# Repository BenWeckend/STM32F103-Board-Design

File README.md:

# STM32F103 Board Design

## Überblick

Hardware-Referenzdesign und Firmware für ein Übungs-Entwicklungsboard auf Basis des **STM32F103C8T6** mit CAN, USB, I²C (BME280) und weiterer Peripherie.

Das Repository enthält:

* KiCad-Schaltplan und PCB-Design
* Gerber- und Fertigungsdaten
* Stückliste (BOM)
* STM32CubeIDE Firmware-Projekt
* Tauri Desktop-Anwendung zur Kommunikation mit dem Board

---

## Hardware

### Schaltplan

<p align="center">
  
</p>

<p align="center">
  Vollständiger Schaltplan des STM32F103-Boards mit CAN, USB, Spannungsversorgung und BME280-Sensor.
</p>

### 3D-Ansicht der Platine

<p align="center">
  
</p>

<p align="center">
  3D-Vorschau der fertig bestückten Leiterplatte aus KiCad.
</p>

---

## Projektstruktur

| Ordner                 | Beschreibung                               |
| ---------------------- | ------------------------------------------ |
| `kicad/`               | Schaltplan, PCB-Layout und Fertigungsdaten |
| `firmware/`            | STM32CubeIDE-Projekt                       |
| `tauri-app/`           | Desktop-Anwendung (Rust + Frontend)        |

---

## Hauptfunktionen

### Mikrocontroller

* `STM32F103C8T6` (LQFP48)

### Kommunikation

* CAN-Bus über `TJA1051`
* USB Micro-B Device Interface

### Sensorik

* `BME280` (I²C)

  * Temperatur
  * Luftdruck
  * Luftfeuchtigkeit

### Spannungsversorgung

* `AMS1117-3.3`
* Onboard 3.3V-Regler

### Debugging & Programmierung

* SWD Header
* ST-Link kompatibel
* STM32CubeProgrammer kompatibel

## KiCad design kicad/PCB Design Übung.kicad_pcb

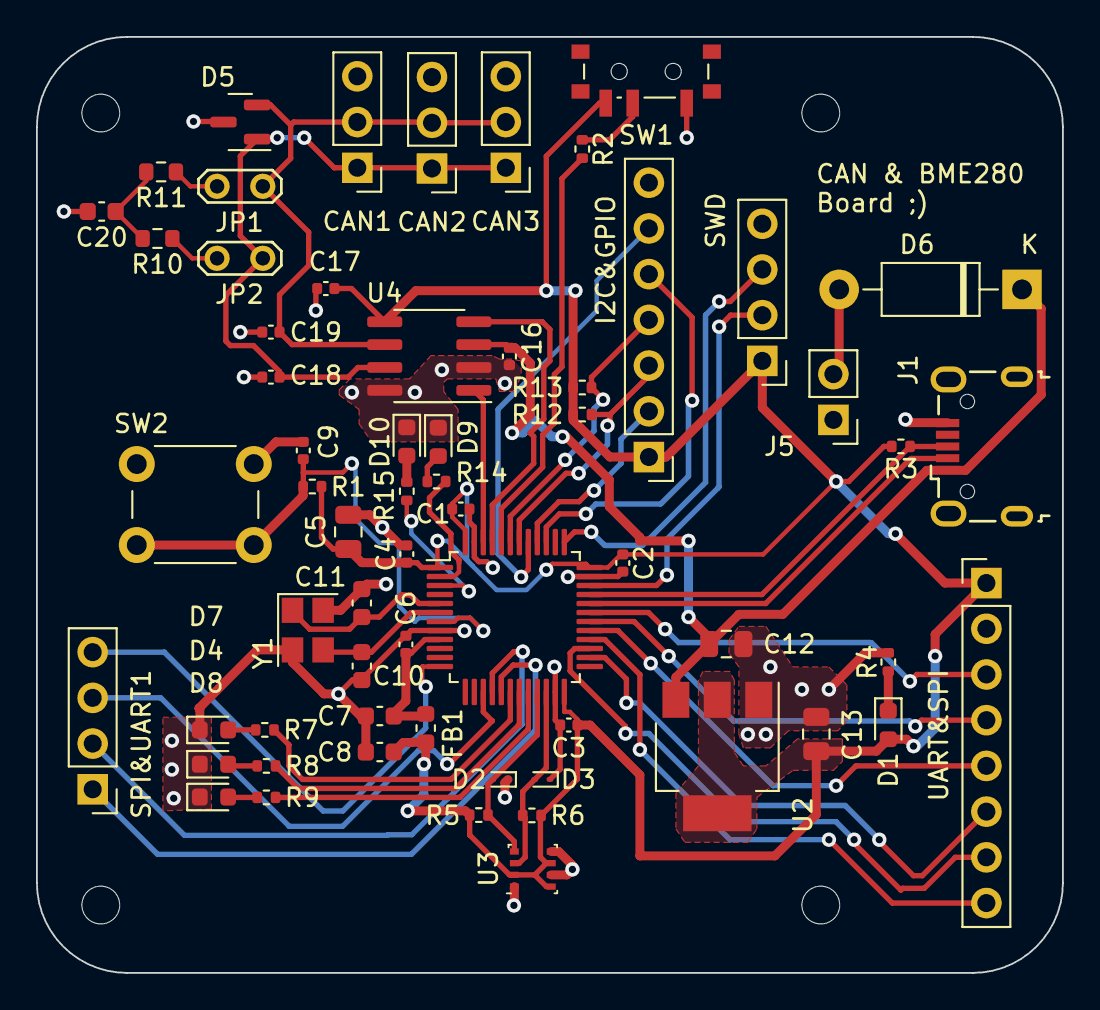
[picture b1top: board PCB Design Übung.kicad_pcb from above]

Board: 2 copper layers, 57.0 x 52.0 mm, 66 parts (0 on the bottom side), 49 nets.

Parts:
C1, C2, C3, C4, C9, C16, C17: 100n; C_0402_1005Metric
C5: 10u; C_0805_2012Metric
C6: 10n; C_0402_1005Metric
C7, C8: 1u; C_0603_1608Metric
C10, C11: 10p; C_0603_1608Metric
C12, C13: 22u; C_0805_2012Metric
C18, C19: 100p; C_0402_1005Metric
C20: 4n7; C_0603_1608Metric
CAN1, CAN2, CAN3: Conn_01x03; PinHeader_1x03_P2.54mm_Vertical
D1: LED-Green; LED_0603_1608Metric
D2, D3: ESD9B3.3ST5G; D_SOD-923
D4, D7, D8: LED_B; LED_0603_1608Metric
D5: NUP2105LT1G; SOT-23
D6: 1N5818; D_DO-41_SOD81_P10.16mm_Horizontal
D9: LED_G; LED_0603_1608Metric
D10: LED_R; LED_0603_1608Metric
FB1: 120R; L_0603_1608Metric
H1, H2, H3, H4: MountingHole; MountingHole_2.1mm
I2C&GPIO: Conn_01x07; PinHeader_1x07_P2.54mm_Vertical
J1: USB_B_Micro; USB_Micro-B_Wuerth_629105150521
J5: Conn_01x02_Pin; PinHeader_1x02_P2.54mm_Vertical
JP1, JP2: Jumper_2_Bridged; TestPoint_2Pads_Pitch2.54mm_Drill0.8mm
R1, R2: 10k; R_0402_1005Metric
R3: 1k5; R_0402_1005Metric
R4, R14: 0.1k; R_0402_1005Metric
R5, R6, R12, R13: 4k7; R_0402_1005Metric
R7, R8, R9: 10ohm; R_0402_1005Metric
R10, R11: 60ohm; R_0603_1608Metric
R15: 220ohm; R_0402_1005Metric
SPI&UART1: Conn_01x04_Pin; PinHeader_1x04_P2.54mm_Vertical
SW1: SW_SPDT; SW_SPDT_PCM12
SW2: SW_Push; SW_PUSH_6mm
SWD: Conn_01x04_Pin; PinHeader_1x04_P2.54mm_Vertical
U1: STM32F103C8T6; LQFP-48_7x7mm_P0.5mm
U2: AMS1117-3.3; SOT-223-3_TabPin2
U3: BME280; Bosch_LGA-8_2.5x2.5mm_P0.65mm_ClockwisePinNumbering
U4: TJA1051T-3; SOIC-8_3.9x4.9mm_P1.27mm
UART&SPI: Conn_01x08; PinHeader_1x08_P2.54mm_Vertical
Y1: 16MHz; Crystal_SMD_3225-4Pin_3.2x2.5mm

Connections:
+3.3V: C1.1, C2.1, C3.1, C4.1, C5.1, C8.1, C13.1, C17.1, D1.2 (A), FB1.2, I2C&GPIO.1, R1.2, R3.1, R5.1, R6.1, R12.1, R13.1, SW1.3 (C), SWD.1, U1.1 (VBAT), U1.24 (VDD), U1.36 (VDD), U1.48 (VDD), U2.2 (VO), U3.2 (CSB), U3.6 (VDDIO), U3.8 (VDD), U4.5 (VIO), UART&SPI.1
+3.3VA: C6.1, C7.1, FB1.1, U1.9 (VDDA)
/BOOT0: R2.2, U1.44 (BOOT0)
/CANH: C18.1, CAN1.1, CAN2.1, CAN3.1, D5.1 (K), JP2.1 (A), U4.7 (CANH)
/CANL: C19.1, CAN1.2, CAN2.2, CAN3.2, D5.2 (K), JP1.1 (A), U4.6 (CANL)
/HSE_IN: C11.1, U1.5 (PD0), Y1.1
/HSE_OUT: C10.1, U1.6 (PD1), Y1.3
/PWR_LED_K: D1.1 (K), R4.1
/SWCLK: SWD.3, U1.37 (PA14)
/SWDIO: SWD.2, U1.34 (PA13)
/SW_BOOT0: R2.1, SW1.2 (B)
/USB_D+: J1.3 (D+), R3.2, U1.33 (PA12)
/USB_D-: J1.2 (D-), U1.32 (PA11)
CAN_RX: U1.45 (PB8), U4.4 (RXD)
CAN_TX: U1.46 (PB9), U4.1 (TXD)
GND: C1.2, C2.2, C3.2, C4.2, C5.2, C6.2, C7.2, C8.2, C9.2, C10.2, C11.2, C12.2, C13.2, C16.2, C17.2, C18.2, C19.2, C20.2, CAN1.3, CAN2.3, CAN3.3, D2.1 (A1), D3.1 (A1), D4.1 (K), D5.3 (A), D7.1 (K), D8.1 (K), D9.1 (K), D10.1 (K), I2C&GPIO.7, J1.5 (GND), J5.1, R4.2, SW1.1 (A), SW2.1, SWD.4, U1.8 (VSSA), U1.23 (VSS), U1.35 (VSS), U1.47 (VSS), U2.1 (GND), U3.1 (GND), U3.5 (SDO), U3.7 (GND), U4.2 (GND), U4.8 (S), UART&SPI.2, Y1.2, Y1.4
I2C1_SCL: I2C&GPIO.3, R12.2, U1.42 (PB6)
I2C1_SDA: I2C&GPIO.4, R13.2, U1.43 (PB7)
NRST: C9.1, R1.1, SW2.2, U1.7 (NRST)
unnamed: C20.1, R10.2, R11.2
unnamed: D4.2 (A), R8.2
unnamed: D6.2 (A), J5.2
unnamed: D7.2 (A), R7.2
unnamed: D8.2 (A), R9.2
unnamed: D9.2 (A), R14.2
unnamed: D10.2 (A), R15.2
unnamed: JP1.2 (B), R11.1
unnamed: JP2.2 (B), R10.1
unnamed: R7.1, U1.18 (PB0)
unnamed: R8.1, U1.19 (PB1)
unnamed: R9.1, U1.20 (PB2)
unnamed: R14.1, U1.2 (PC13)
unnamed: R15.1, U1.3 (PC14)
PB3: I2C&GPIO.5, U1.39 (PB3)
PB4: I2C&GPIO.2, U1.40 (PB4)
PB5: I2C&GPIO.6, U1.41 (PB5)
SCL_I2C: D2.2 (A2), R5.2, U1.21 (PB10), U3.4 (SCK)
SDA_I2C: D3.2 (A2), R6.2, U1.22 (PB11), U3.3 (SDI)
SPI1_MISO: SPI&UART1.2, U1.16 (PA6)
SPI1_MOSI: SPI&UART1.1, U1.17 (PA7)
SPI1_SCK: SPI&UART1.3, U1.15 (PA5)
SPI2_MISO: U1.27 (PB14), UART&SPI.7
SPI2_MOSI: U1.28 (PB15), UART&SPI.8
SPI2_SCK: U1.26 (PB13), UART&SPI.6
UART_TX: SPI&UART1.4, U1.12 (PA2)
USART1_CK: U1.29 (PA8), UART&SPI.5
USART1_RX: U1.31 (PA10), UART&SPI.3
USART1_TX: U1.30 (PA9), UART&SPI.4
VBUS: C12.1, C16.1, D6.1 (K), J1.1 (VBUS), U2.3 (VI), U4.3 (VCC)

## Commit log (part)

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2026-05-25 app setup
2026-06-07 Update README with schematic and 3D construction images
    Added images and description for schematic and 3D construction.
2026-06-07 Revise README for STM32F103 Board Design details
    Updated README.md to provide a comprehensive overview of the STM32F103 Board Design, including hardware references, project structure, main features, and firmware development instructions.
2026-06-07 Remove manufacturing section from README
    Removed manufacturing section and related details from README.
